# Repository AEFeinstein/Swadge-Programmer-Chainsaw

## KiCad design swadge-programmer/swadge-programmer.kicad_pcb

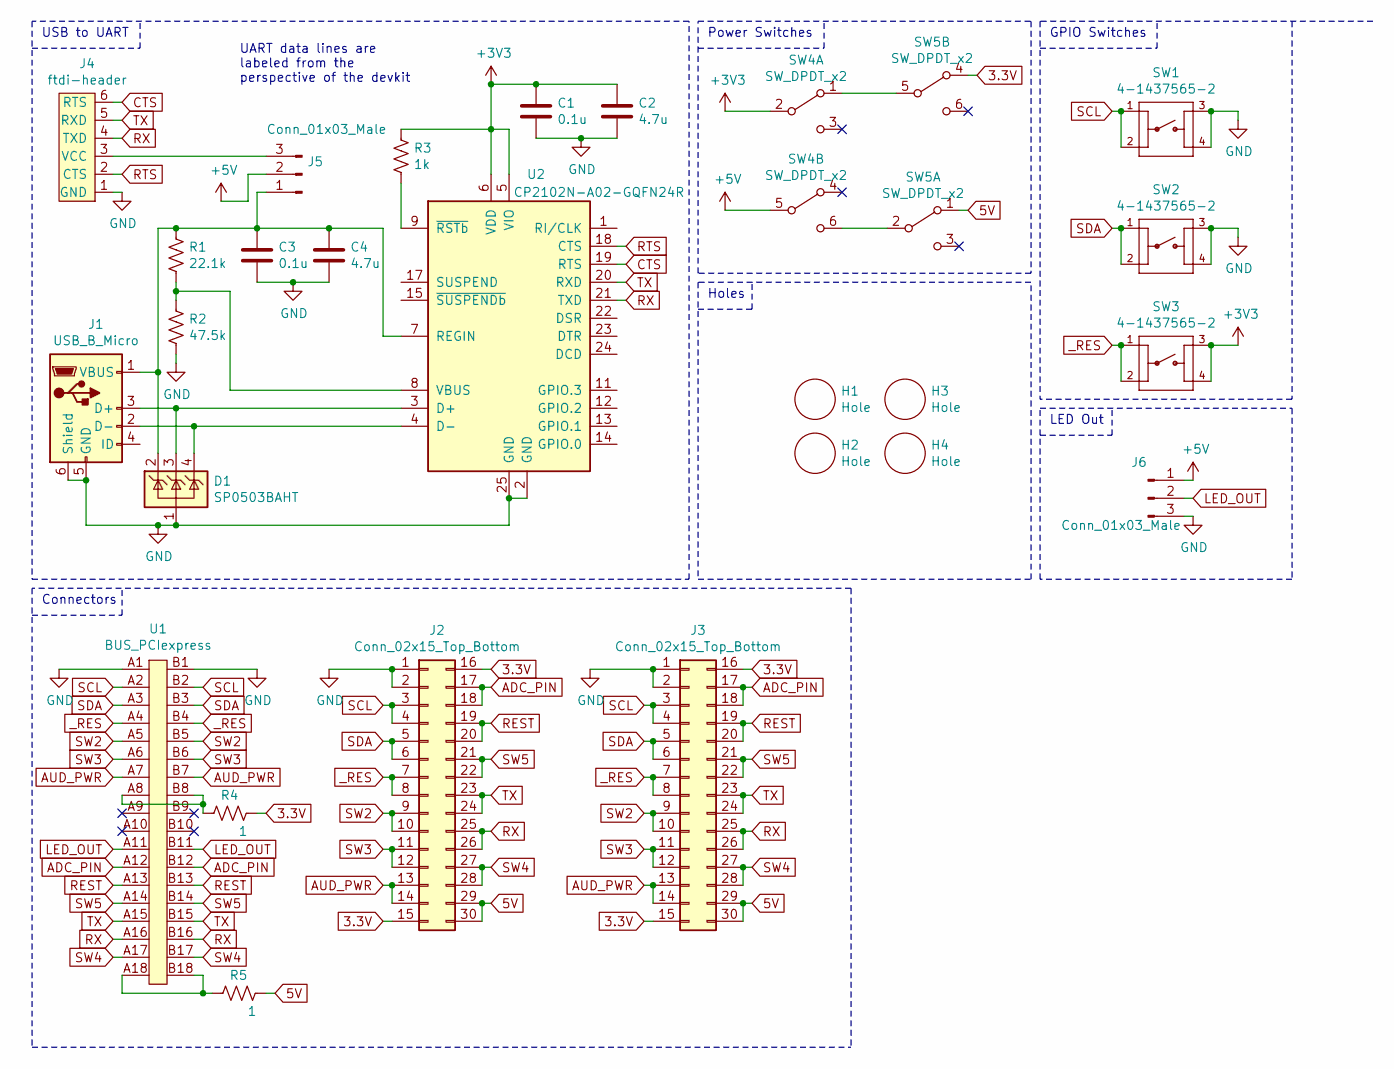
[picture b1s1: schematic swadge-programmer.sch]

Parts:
C1, C3: 0.1u; C_0603_1608Metric; Digikey 1276-1000-1-ND
C2, C4: 4.7u; C_0603_1608Metric; Digikey 1276-1045-1-ND
D1: SP0503BAHT; SOT-143; Digikey F2715CT-ND
H1, H2, H3, H4: Hole; Digikey 2042-1007-ND
J1: USB_B_Micro; USB_Micro-B_Molex_47346-0001; Digikey WM17141CT-ND
J2, J3: Conn_02x15_Top_Bottom; PinHeader_2x15_P2.54mm_Vertical; Digikey S2012EC-15-ND
J4: ftdi-header; Digikey n/a
J5, J6: Conn_01x03_Male; PinHeader_1x03_P2.54mm_Vertical; Digikey 1849-1003-ND
R1: 22.1k; R_0603_1608Metric; Digikey RMCF0603FT22K1CT-ND
R2: 47.5k; R_0603_1608Metric; Digikey P47.5KHCT-ND
R3: 1k; R_0603_1608Metric; Digikey 311-1.00KHRCT-ND
R4, R5: 1; R_Axial_DIN0207_L6.3mm_D2.5mm_P10.16mm_Horizontal; Digikey RNF14FTD1R00CT-ND
SW1, SW2, SW3: 4-1437565-2; SW_4-1437565-2; MPN FSM4JSMATR; Digikey 450-1759-1-ND
SW4, SW5: SW_DPDT_x2; JS202011CQN; Digikey 401-2001-ND
U1: BUS_PCIexpress; 10018784-10210TLF; Digikey 609-2029-ND
U2: CP2102N-A02-GQFN24R; QFN-24-1EP_4x4mm_P0.5mm_EP2.6x2.6mm; Digikey 336-5888-1-ND

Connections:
3.3V: J2.15, J2.16, J3.15, J3.16, R4.2, SW5.4 (A)
5V: J2.29, J2.30, J3.29, J3.30, R5.2, SW5.1 (A)
+3V3: C1.1, C2.1, R3.2, SW3.3, SW3.4, SW4.2 (B), U2.5 (VIO), U2.6 (VDD)
+5V: J5.2, J6.1, SW4.5 (B)
ADC_PIN: J2.17, J2.18, J3.17, J3.18, U1.A12, U1.B12
AUD_PWR: J2.13, J2.14, J3.13, J3.14, U1.A7, U1.B7
CTS: J4.6 (RTS), U2.19 (RTS)
GND: C1.2, C2.2, C3.2, C4.2, D1.1 (A), J1.5 (GND), J1.6 (Shield), J2.1, J2.2, J3.1, J3.2, J4.1 (GND), J6.3, R2.2, SW1.3, SW1.4, SW2.3, SW2.4, U1.A1, U1.B1, U2.2 (GND), U2.25 (GND)
LED_OUT: J6.2, U1.A11, U1.B11
unnamed: C3.1, C4.1, D1.2 (K), J1.1 (VBUS), J5.1, R1.1, U2.7 (REGIN)
unnamed: D1.3 (K), J1.3 (D+), U2.3 (D+)
unnamed: D1.4 (K), J1.2 (D-), U2.4 (D-)
unnamed: J4.3 (VCC), J5.3
unnamed: R1.2, R2.1, U2.8 (VBUS)
unnamed: R3.1, U2.9 (~RSTb)
unnamed: R4.1, U1.A8, U1.B8
unnamed: R5.1, U1.A18, U1.B18
unnamed: SW4.1 (A), SW5.5 (B)
unnamed: SW4.6 (C), SW5.2 (B)
REST: J2.19, J2.20, J3.19, J3.20, U1.A13, U1.B13
RTS: J4.2 (CTS), U2.18 (CTS)
RX: J2.25, J2.26, J3.25, J3.26, J4.4 (TXD), U1.A16, U1.B16, U2.21 (TXD)
SCL: J2.3, J2.4, J3.3, J3.4, SW1.1, SW1.2, U1.A2, U1.B2
SDA: J2.5, J2.6, J3.5, J3.6, SW2.1, SW2.2, U1.A3, U1.B3
SW2: J2.9, J2.10, J3.9, J3.10, U1.A5, U1.B5
SW3: J2.11, J2.12, J3.11, J3.12, U1.A6, U1.B6
SW4: J2.27, J2.28, J3.27, J3.28, U1.A17, U1.B17
SW5: J2.21, J2.22, J3.21, J3.22, U1.A14, U1.B14
TX: J2.23, J2.24, J3.23, J3.24, J4.5 (RXD), U1.A15, U1.B15, U2.20 (RXD)
_RES: J2.7, J2.8, J3.7, J3.8, SW3.1, SW3.2, U1.A4, U1.B4

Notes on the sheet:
Power Switches
GPIO Switches
USB to UART
Connectors
Holes
UART data lines are labeled from the perspective of the devkit
LED Out

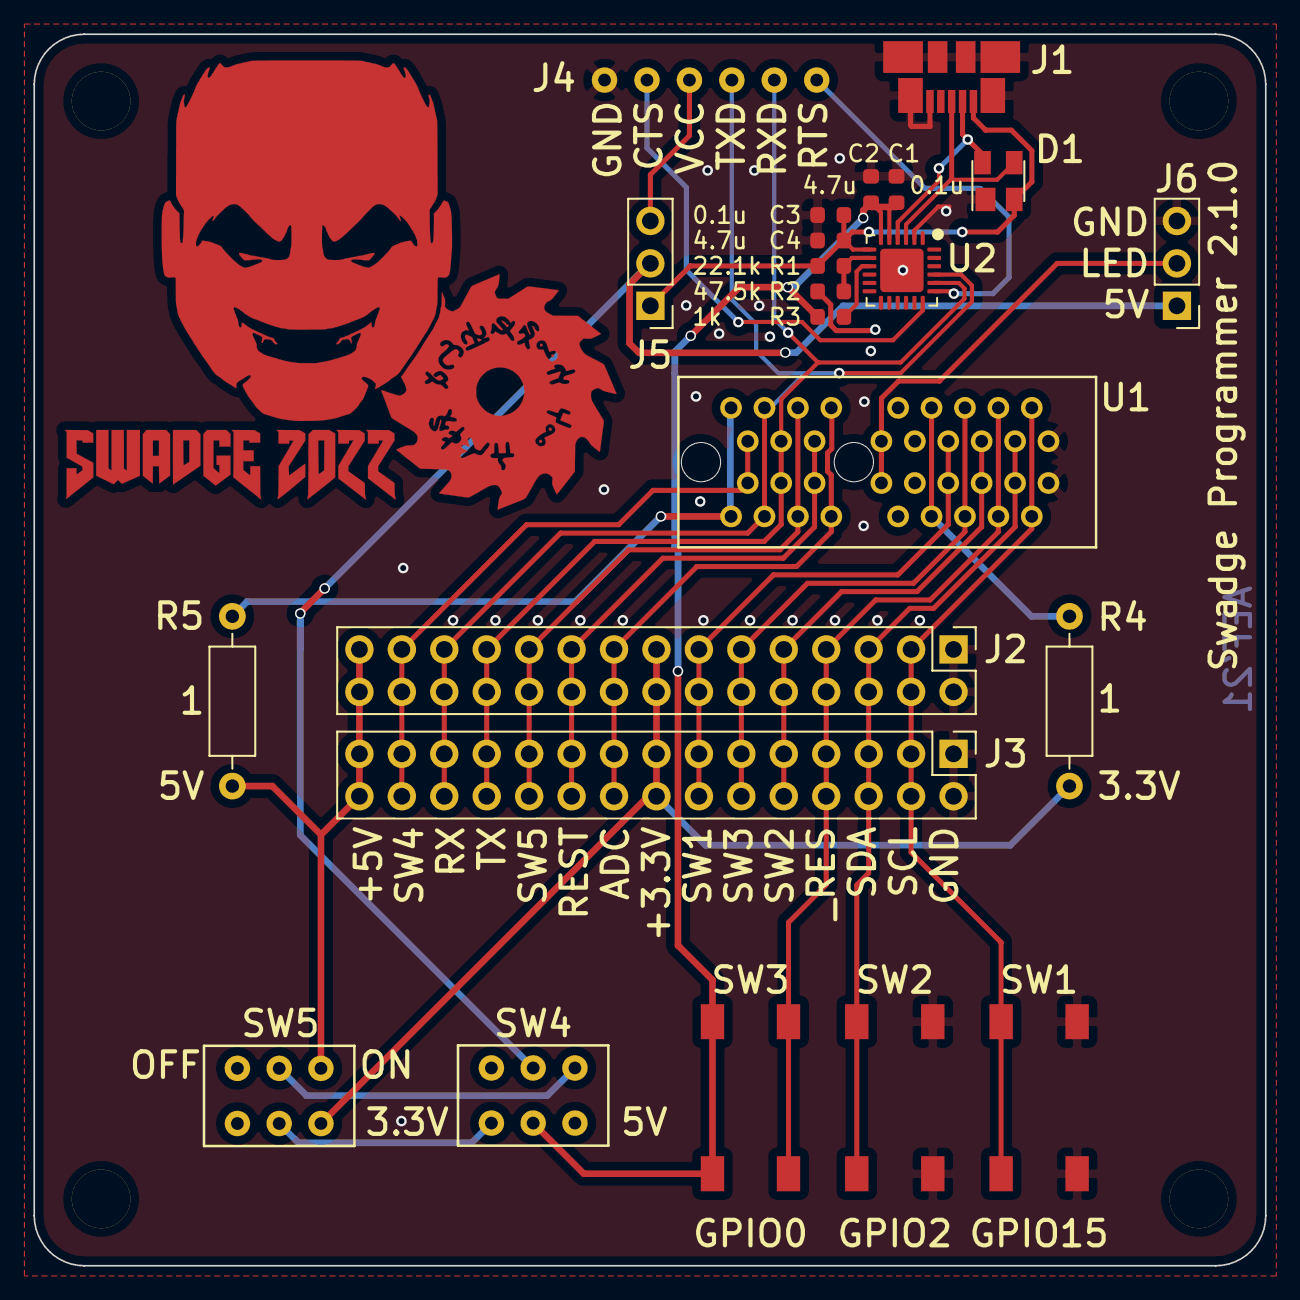
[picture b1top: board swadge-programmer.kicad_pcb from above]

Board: 2 copper layers, 73.7 x 73.7 mm, 28 parts (0 on the bottom side), 30 nets.

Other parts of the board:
Ref**: Val**; programmer-graphic

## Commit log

2021-07-30 Initial commit copied from Swadge 2020 HW repo
2021-08-03 Move and reroute programmer
2021-08-03 Fix 3D model references
2021-08-03 Cleanup text and tracks
2021-08-03 Round corners, clean up text
2021-08-03 Update text
2021-08-04 Adjusted PCIe position
2021-08-04 Added missing vias
2021-08-17 Added graphic to programmer
2021-08-17 Added pin for LED OUT
2021-08-18 Updated CP2012n revision
2021-08-18 Added signature
2021-08-18 Fixed board params
2021-08-18 Added output directory
2021-08-18 Removed output files, added BOM processor
2021-10-04 Added jumpers to CAD, flipped 5V switch
